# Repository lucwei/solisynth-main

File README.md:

# Solisynth
Solisynth is an open source modular synthesizer project. 

# License
The following license is used in the project, unless specified differently in a particular subfolder:

Schematics, PCBs: [CERN-OHL-S v2](https://ohwr.org/cern_ohl_s_v2.txt)

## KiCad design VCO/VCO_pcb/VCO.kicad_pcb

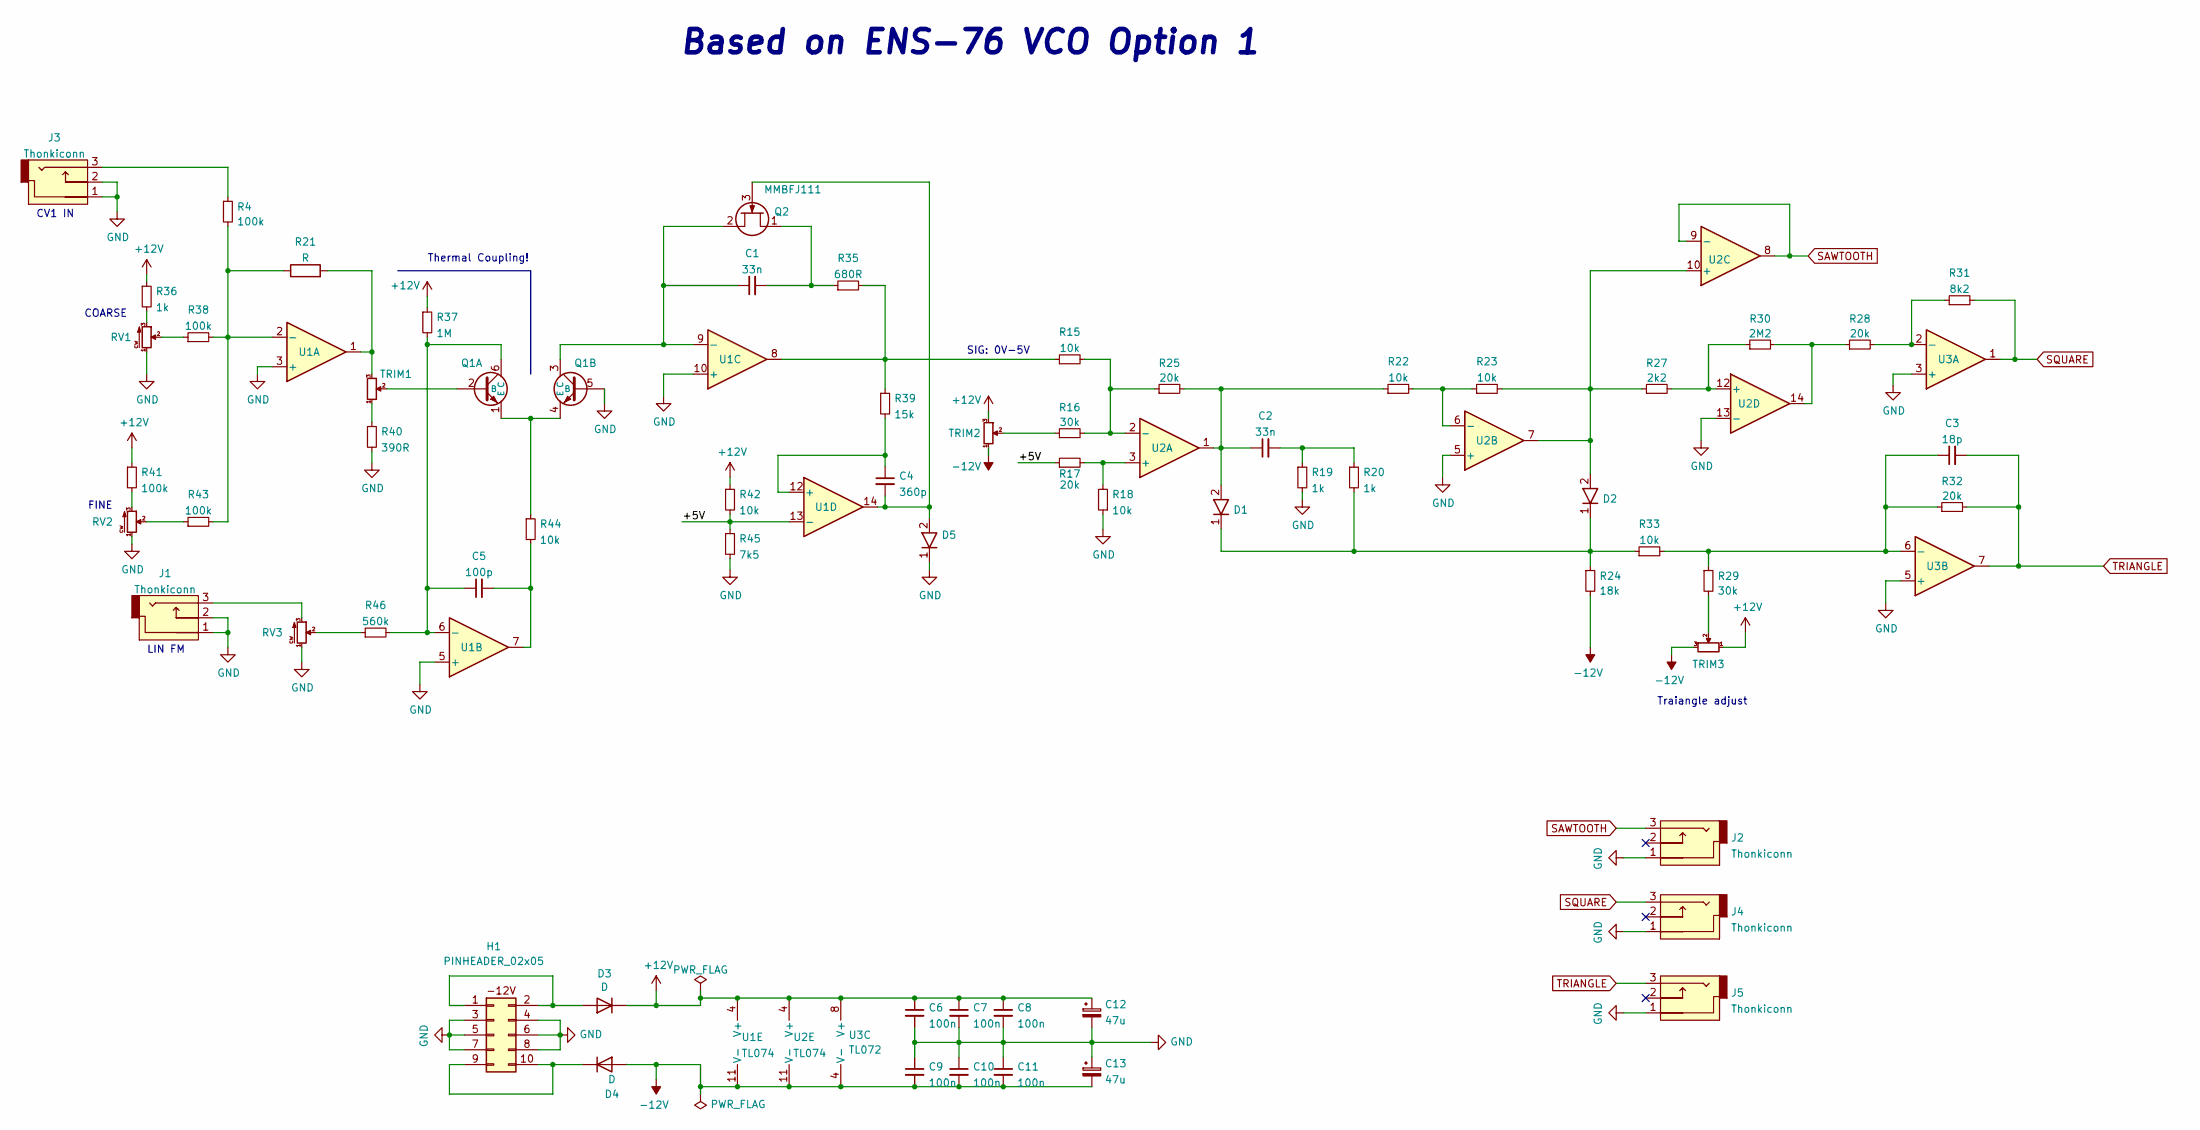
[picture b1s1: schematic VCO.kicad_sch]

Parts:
C1, C2: 33n; C_0603_1608Metric; Voltage 50V; Tolerance 10%; MPN CL10B333KB8NNNC
C3: 18p; C_0603_1608Metric; Voltage 50V; Tolerance 5%; MPN CL10C180JB81PNC
C4: 360p; C_0603_1608Metric; Voltage 50V; Tolerance 5%; MPN GRM1885C1H361JA01D
C5: 100p; C_0603_1608Metric; Voltage 50V; Tolerance 5%; MPN CL10C101JB8NNNC
C6, C7, C8, C9, C10, C11: 100n; C_0603_1608Metric; Voltage 50V; Tolerance 5%; MPN CL10B104JB8NNNC
C12, C13: 47u; CP_Elec_6.3x5.4; Voltage 25V; Tolerance 20%; MPN 865080443007
D1, D2, D5: D; SOD-123; MPN SBA130AS_R1_00001
D3, D4: D; D_SOD-123; MPN SBA130AS_R1_00001
H1: PINHEADER_02x05; Modular_Power_Header_2x05_P2.54mm_Vertical
J1, J2, J3, J4, J5: Thonkiconn; WQP-PJ398SM; MPN WQP-PJ398SM
Q1: BCM847BS,115; SOT65P210X110-6N; MPN BCM847BS,115
Q2: MMBFJ111; SOT-23; MPN MMBFJ111
R4, R38, R41, R43: 100k; R_0603_1608Metric; Tolerance 1%; MPN CR0603-FX-1003ELF
R15, R18, R22, R23, R33, R42, R44: 10k; R_0603_1608Metric; Tolerance 1%; MPN CR0603-FX-1002ELF
R16, R29: 30k; R_0603_1608Metric; Tolerance 1%; MPN CR0603-FX-3002ELF
R17: 20k; R_0603_1608Metric; MPN CR0603-FX-2002ELF; LCSC C4184
R19, R20, R36: 1k; R_0603_1608Metric; Tolerance 1%; MPN CR0603-FX-1001ELF
R21: R; R_Axial_DIN0204_L3.6mm_D1.6mm_P5.08mm_Horizontal; MPN TFPTL15L2201JL2B
R24: 18k; R_0603_1608Metric; Tolerance 1%; MPN CR0603-FX-1802ELF
R25, R28, R32: 20k; R_0603_1608Metric; Tolerance 1%; MPN CR0603-FX-2002ELF
R27: 2k2; R_0603_1608Metric; Tolerance 1%; MPN CR0603-FX-2201ELF
R30: 2M2; R_0603_1608Metric; Tolerance 1%; MPN RC0603FR-132M2L
R31: 8k2; R_0603_1608Metric; Tolerance 1%; MPN CR0603-FX-8201ELF; LCSC C114637
R35: 680R; R_0603_1608Metric; Tolerance 1%; MPN CR0603-FX-6800ELF
R37: 1M; R_0603_1608Metric; Tolerance 1%; MPN CR0603-FX-1004ELF
R39: 15k; R_0603_1608Metric; Tolerance 1%; MPN CR0603-FX-1502ELF
R40: 390R; R_0603_1608Metric; Tolerance 1%; MPN CR0603-FX-3900ELF
R45: 7k5; R_0603_1608Metric; Tolerance 1%; MPN CR0603-FX-7501ELF; LCSC C3016324
R46: 560k; R_0603_1608Metric; Tolerance 1%; MPN CR0603-FX-5603ELF
RV1: RK09L1140A66; RK09L; MPN RK09L1140A66
RV2, RV3: PTV09A-4025U-B103; PTV09A; MPN PTV09A-4025U-B103
TRIM1: 3362P-1-101LF; 3362P; MPN 3362P-1-101LF
TRIM2, TRIM3: 3362P-1-104LF; 3362P; MPN 3362P-1-104LF
U1, U2: TL074; SOIC-14_3.9x8.7mm_P1.27mm; MPN TL074
U3: TL072; SOIC-8_3.9x4.9mm_P1.27mm; MPN TL072

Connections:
+12V: C6.1, C7.1, C8.1, C12.1, D3.1 (K), R36.1, R37.1, R41.1, R42.1, TRIM2.3, TRIM3.1, U1.4 (V+), U2.4 (V+), U3.8 (V+)
-12V: C9.2, C10.2, C11.2, C13.2, D4.2 (A), R24.2, TRIM2.1, TRIM3.3, U1.11 (V-), U2.11 (V-), U3.4 (V-)
/+5V: R17.1, R42.2, R45.1, U1.13 (-)
GND: C6.2, C7.2, C8.2, C9.1, C10.1, C11.1, C12.2, C13.1, D5.1, H1.3, H1.4, H1.5, H1.6, H1.7, H1.8, J1.1, J1.2, J2.1, J3.1, J3.2, J4.1, J5.1, Q1.5 (B), R18.1, R19.2, R40.2, R45.2, RV1.1, RV2.1, RV3.1, U1.3 (+), U1.5 (+), U1.10 (+), U2.5 (+), U2.13 (-), U3.3 (+), U3.5 (+)
unnamed: C1.1, Q1.3 (C), Q2.2 (S), U1.9 (-)
unnamed: C1.2, Q2.1 (D), R35.1
unnamed: C2.1, D1.2, R22.1, R25.2, U2.1
unnamed: C2.2, R19.1, R20.1
unnamed: C3.1, R29.1, R32.1, R33.2, U3.6 (-)
unnamed: C4.1, R39.2, U1.12 (+)
unnamed: C4.2, D5.2, Q2.3 (G), U1.14
unnamed: C5.1, Q1.6 (C), R37.2, R46.2, U1.6 (-)
unnamed: C5.2, R44.2, U1.7
unnamed: D1.1, D2.1, R20.2, R24.1, R33.1
unnamed: D2.2, R23.2, R27.1, U2.7, U2.10 (+)
unnamed: D3.2 (A), H1.1, H1.2
unnamed: D4.1 (K), H1.9, H1.10
unnamed: J1.3, RV3.3
unnamed: J3.3, R4.1
unnamed: Q1.1 (E), Q1.4 (E), R44.1
unnamed: Q1.2 (B), TRIM1.2
unnamed: R15.1, R35.2, R39.1, U1.8
unnamed: R15.2, R16.2, R25.1, U2.2 (-)
unnamed: R16.1, TRIM2.2
unnamed: R17.2, R18.2, U2.3 (+)
unnamed: R4.2, R21.1, R38.2, R43.2, U1.2 (-)
unnamed: R21.2, TRIM1.3, U1.1
unnamed: R22.2, R23.1, U2.6 (-)
unnamed: R27.2, R30.1, U2.12 (+)
unnamed: R28.1, R30.2, U2.14
unnamed: R28.2, R31.1, U3.2 (-)
unnamed: R36.2, RV1.3
unnamed: R38.1, RV1.2
unnamed: R40.1, TRIM1.1
unnamed: R41.2, RV2.3
unnamed: R43.1, RV2.2
unnamed: R46.1, RV3.2
unnamed: R29.2, TRIM3.2
SAWTOOTH: J2.3, U2.8, U2.9 (-)
SQUARE: J4.3, R31.2, U3.1
TRIANGLE: C3.2, J5.3, R32.2, U3.7

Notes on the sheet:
CV1 IN
SIG: 0V-5V
Based on ENS-76 VCO Option 1
Traiangle adjust
FINE
LIN FM
COARSE
Thermal Coupling!

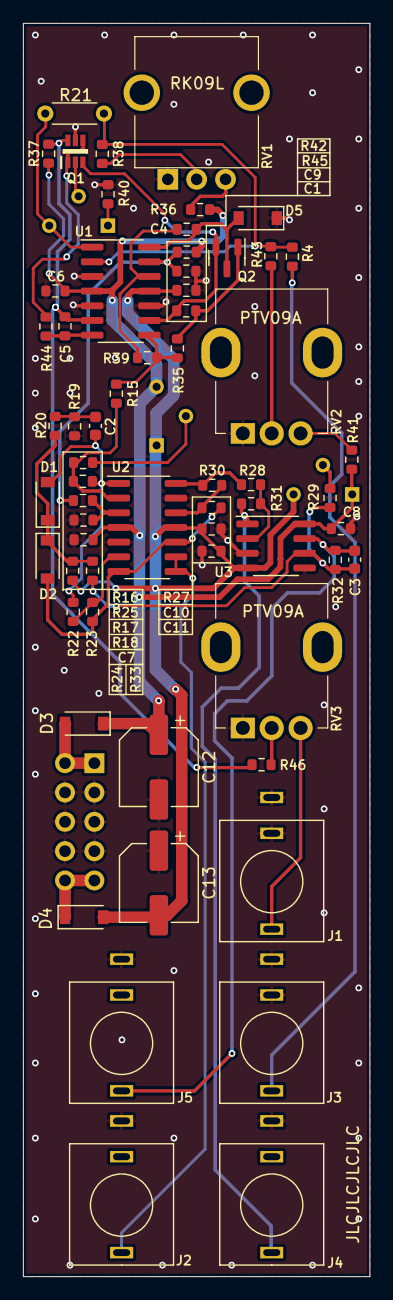
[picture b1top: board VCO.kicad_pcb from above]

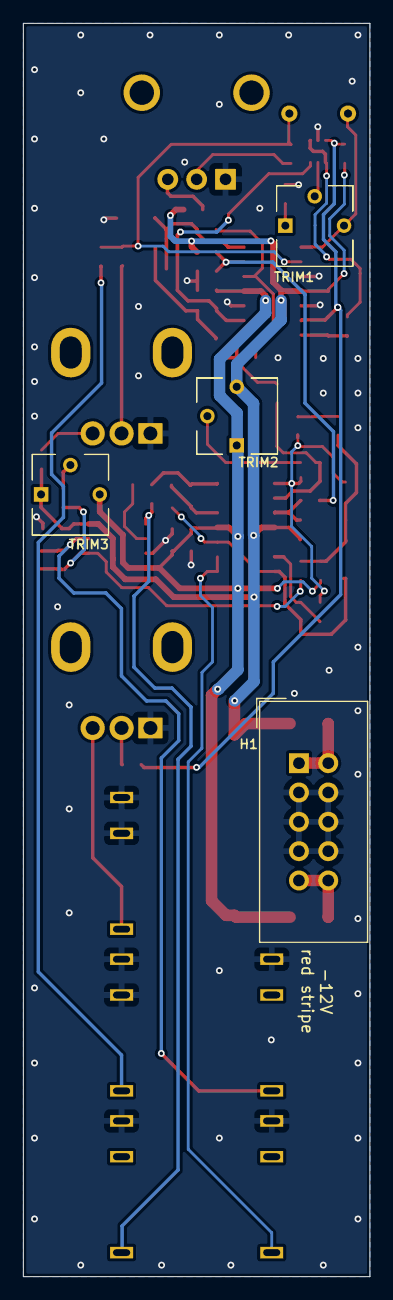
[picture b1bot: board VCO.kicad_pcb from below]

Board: 2 copper layers, 30.0 x 108.5 mm, 66 parts (4 on the bottom side), 41 nets.

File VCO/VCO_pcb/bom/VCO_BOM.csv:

VCO_V1 – BOM,,,,
Qty,Reference,Value,Manufacturer,Partnumber
2,"C1,C2",33n,Samsung Electro-Mechanics,CL10B333KB8NNNC
1,C3,18p,Samsung Electro-Mechanics,CL10C180JB81PNC
1,C4,360p,Murata Electronics,GRM1885C1H361JA01D
1,C5,100p,Samsung Electro-Mechanics,CL10C101JB8NNNC
6,C6-C11,100n,Samsung Electro-Mechanics,CL10B104JB8NNNC
2,"C12,C13",47u,Würth Elektronik,865080443007
5,"D1,D2,D3, D4,D5",SBA130AS_R1_00001,Panjit International Inc.,SBA130AS_R1_00001
1,H1,PINHEADER_02x05,Würth Elektronik,61201021621
5,J1-J5,Thonkiconn,Thonk,WQP-PJ398SM
1,Q1,"BCM847BS,115",Nexperia,"BCM847BS,115"
1,Q2,MMBFJ111,Onsemi,MMBFJ111
1,R16,30k,Bourns,CR0603-FX-3002ELF
3,"R19,R20,R36",1k,Bourns,CR0603-FX-1001ELF
1,R21,R,Vishay / Dale,TFPTL15L2201JL2B
7,"R15,R18,R22,R23,R33,R42,R44",10k,Bourns,CR0603-FX-1002ELF
1,R24,18k,Bourns,CR0603-FX-1802ELF
1,R27,2k2,Bourns,CR0603-FX-2201ELF
2,"R29,R37",1M,Bourns,CR0603-FX-1004ELF
1,R30,2M2,Yageo,RC0603FR-132M2L
1,R31,8k2,Bourns,CR0603-FX-8201ELF
4,"R17,R25,R28,R32",20k,Bourns,CR0603-FX-2002ELF
1,R35,680R,Bourns,CR0603-FX-6800ELF
1,R39,15k,Bourns,CR0603-FX-1502ELF
1,R40,390R,Bourns,CR0603-FX-3900ELF
4,"R4,R38,R41,R43",100k,Bourns,CR0603-FX-1003ELF
1,R45,7k5,Bourns,CR0603-FX-7501ELF
1,R46,560k,Bourns,CR0603-FX-5603ELF
1,RV1,RK09L1140A66,Alps,RK09L1140A66
2,"RV2,RV3",PTV09A-4025U-B103,Bourns,PTV09A-4025U-B103
1,TRIM1,3362P-1-101LF,Bourns,3362P-1-101LF
2,"TRIM2,TRIM3",3362P-1-104LF,Bourns,3362P-1-104LF
2,"U1,U2",TL074,Texas Instruments,TL074
1,U3,TL072,Texas Instruments,TL072
,,,,
,,,,
,,,,
Cable,,,,
1,,PINHEADER_FEMALE_02x08,Würth Elektronik,61201623021
1,,PINHEADER_FEMALE_02x05,Würth Elektronik,61201023021
1,,Flatband cable 10cm,,

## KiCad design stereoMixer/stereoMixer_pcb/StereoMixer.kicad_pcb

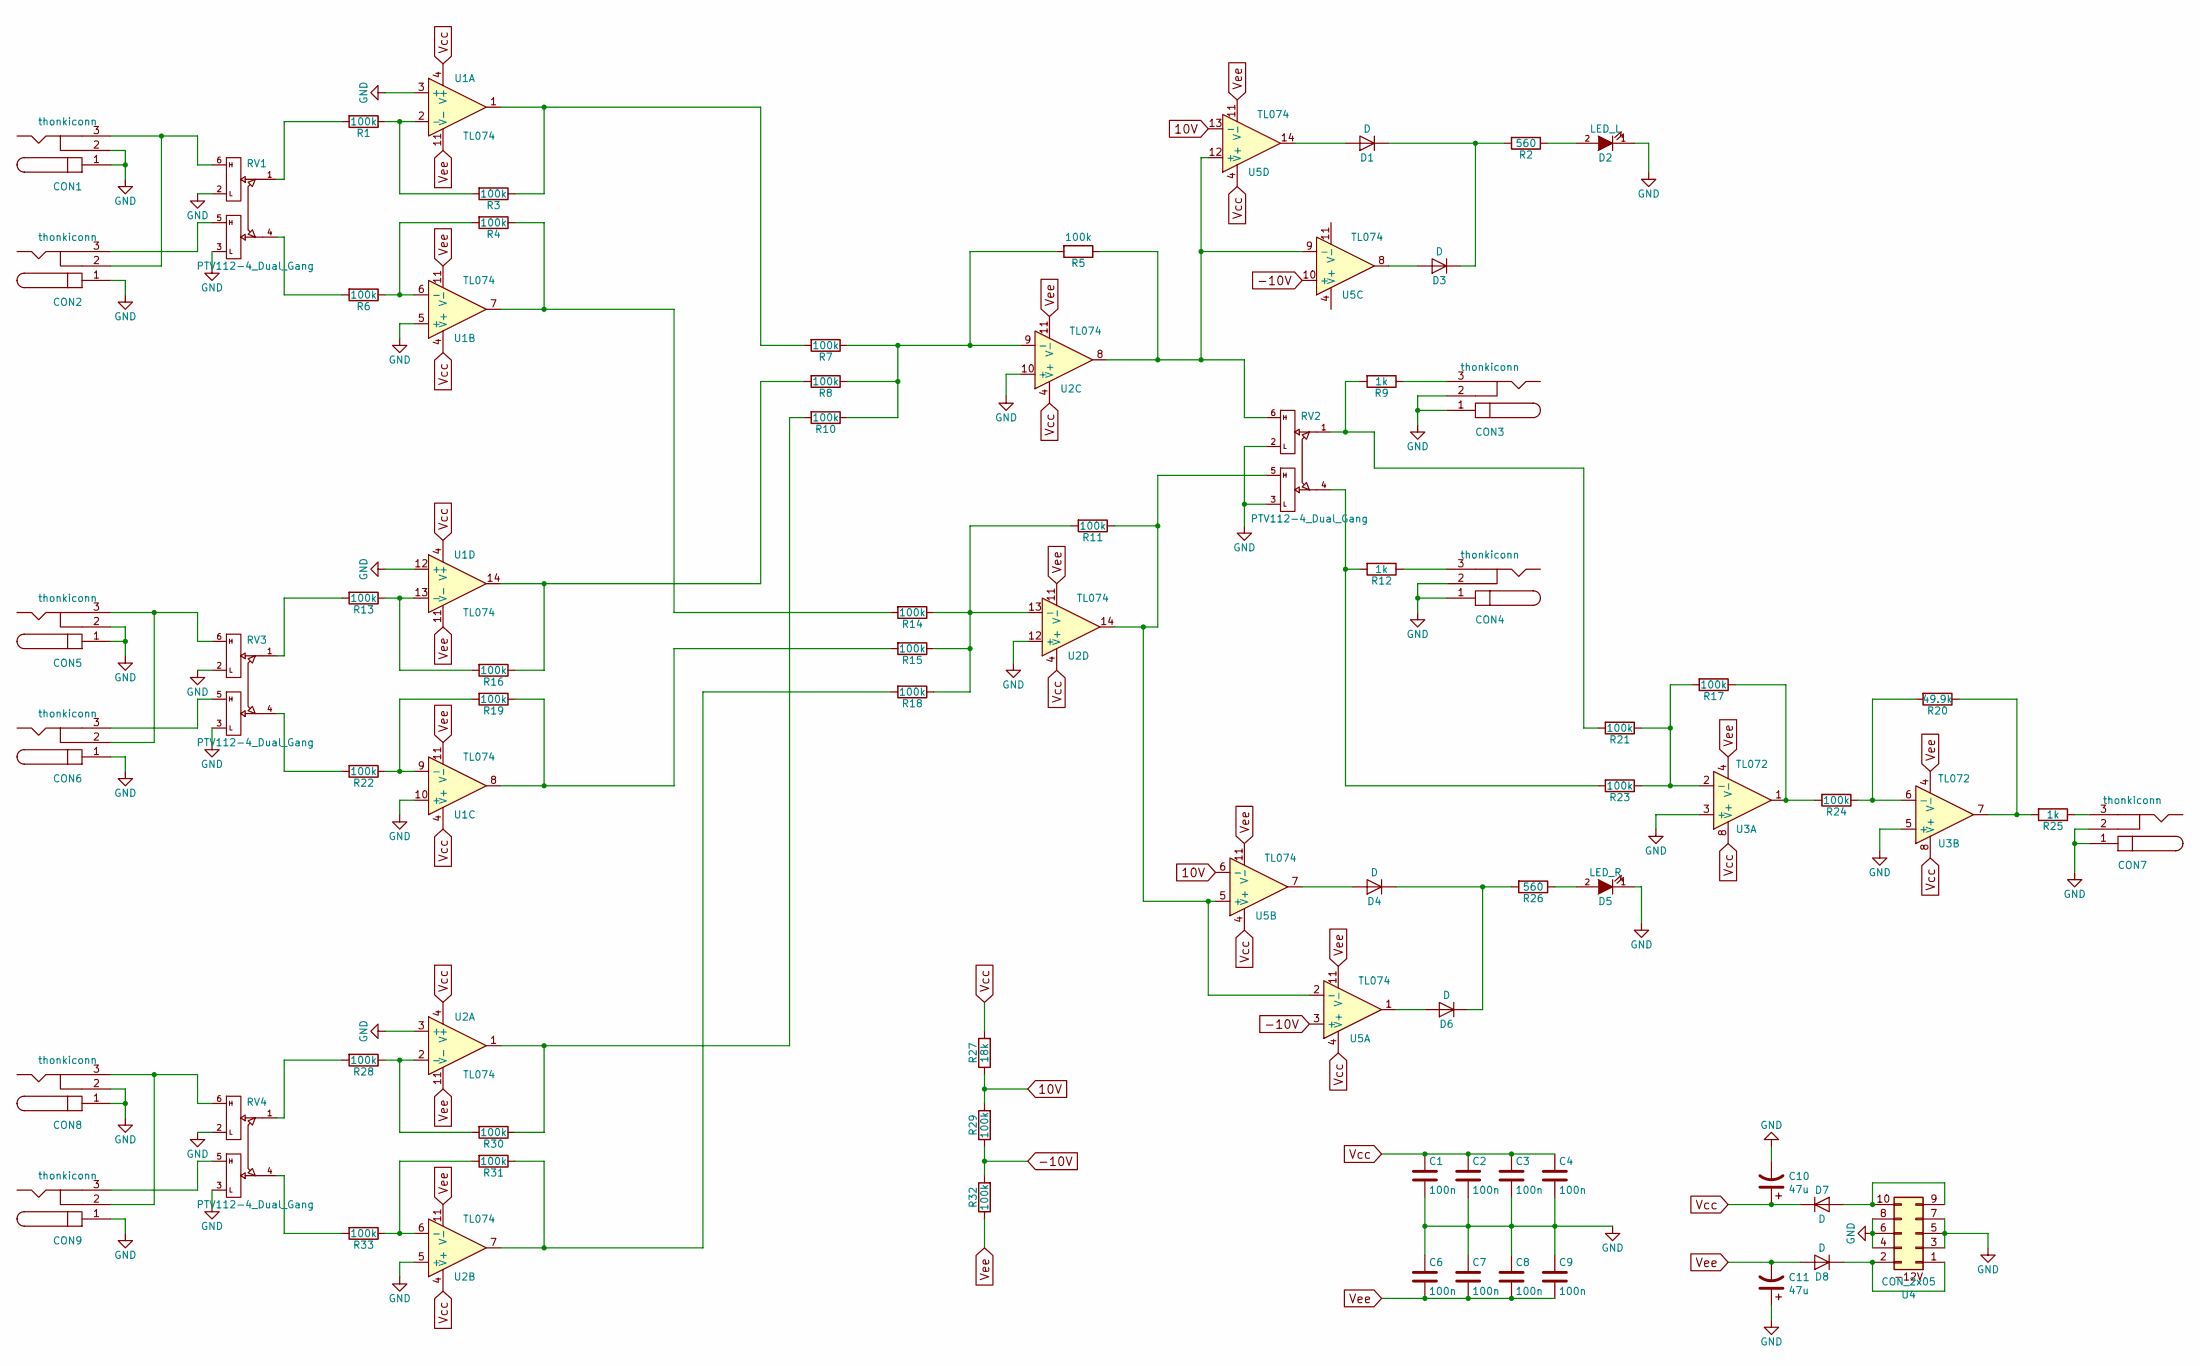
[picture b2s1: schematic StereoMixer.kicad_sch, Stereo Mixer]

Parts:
C1, C2, C3, C4, C6, C7, C8, C9: 100n; C_0603_HandSoldering
C10, C11: 47u; CP_Elec_5x3.9
CON1, CON2, CON3, CON4, CON5, CON6, CON7, CON8, CON9: thonkiconn; THONKICONN
D1, D3, D4, D6, D7, D8: D; D_0603_1608Metric_Pad1.05x0.95mm_HandSolder
D2: LED_L; LED_D3.0mm
D5: LED_R; LED_D3.0mm
R1, R3, R4, R5, R6, R7, R8, R10, R11, R13, R14, R15, R16, R17, R18, R19, R21, R22, R23, R24, R28, R29, R30, R31, R32, R33: 100k; R_0603_HandSoldering
R2, R26: 560; R_0603_HandSoldering
R9, R12, R25: 1k; R_0603_HandSoldering
R20: 49.9k; R_0603_HandSoldering
R27: 18k; R_0603_HandSoldering
RV1, RV2, RV3, RV4: PTV112-4_Dual_Gang; PTV112
U1, U2, U5: TL074; SOIC-14_3.9x8.7mm_Pitch1.27mm
U3: TL072; SOIC-8_3.9x4.9mm_P1.27mm
U4: CON_2x05; Modular_Power_Header_2x05_P2.54mm_Vertical

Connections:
10V: R27.1, R29.2, U5.6 (-), U5.13 (-)
-10V: R29.1, R32.2, U5.3 (+), U5.10 (+)
unnamed: CON1.3, CON2.2, RV1.6
unnamed: CON2.3, RV1.5
unnamed: CON3.3, R9.1
unnamed: CON4.3, R12.1
unnamed: CON5.3, CON6.2, RV3.6
unnamed: CON6.3, RV3.5
unnamed: CON7.3, R25.1
unnamed: CON8.3, CON9.2, RV4.6
unnamed: CON9.3, RV4.5
unnamed: D1.1 (K), D3.1 (K), R2.2
unnamed: D1.2 (A), U5.14
unnamed: D2.2 (A), R2.1
unnamed: D3.2 (A), U5.8
unnamed: D4.1 (K), D6.1 (K), R26.2
unnamed: D4.2 (A), U5.7
unnamed: D5.2 (A), R26.1
unnamed: D6.2 (A), U5.1
unnamed: D7.2 (A), U4.9, U4.10
unnamed: D8.1 (K), U4.1, U4.2
unnamed: R1.1, R3.2, U1.2 (-)
unnamed: R1.2, RV1.1
unnamed: R3.1, R7.2, U1.1
unnamed: R4.2, R6.1, U1.6 (-)
unnamed: R5.1, RV2.6, U2.8, U5.9 (-), U5.12 (+)
unnamed: R6.2, RV1.4
unnamed: R5.2, R7.1, R8.1, R10.1, U2.9 (-)
unnamed: R10.2, R30.1, U2.1
unnamed: R11.1, RV2.5, U2.14, U5.2 (-), U5.5 (+)
unnamed: R11.2, R14.1, R15.1, R18.1, U2.13 (-)
unnamed: R12.2, R23.2, RV2.4
unnamed: R13.1, R16.2, U1.13 (-)
unnamed: R13.2, RV3.1
unnamed: R4.1, R14.2, U1.7
unnamed: R15.2, R19.1, U1.8
unnamed: R8.2, R16.1, U1.14
unnamed: R17.1, R24.2, U3.1
unnamed: R17.2, R21.1, R23.1, U3.2 (-)
unnamed: R18.2, R31.1, U2.7
unnamed: R19.2, R22.1, U1.9 (-)
unnamed: R20.1, R25.2, U3.7
unnamed: R20.2, R24.1, U3.6 (-)
unnamed: R9.2, R21.2, RV2.1
unnamed: R22.2, RV3.4
unnamed: R28.1, R30.2, U2.2 (-)
unnamed: R28.2, RV4.1
unnamed: R31.2, R33.1, U2.6 (-)
unnamed: R33.2, RV4.4
Vcc: C1.1, C2.1, C3.1, C4.1, C10.1, D7.1 (K), R27.2, U1.4 (V+), U2.4 (V+), U3.8 (V+), U5.4 (V+)
Vee: C6.2, C7.2, C8.2, C9.2, C11.2, D8.2 (A), R32.1, U1.11 (V-), U2.11 (V-), U3.4 (V-), U5.11 (V-)

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
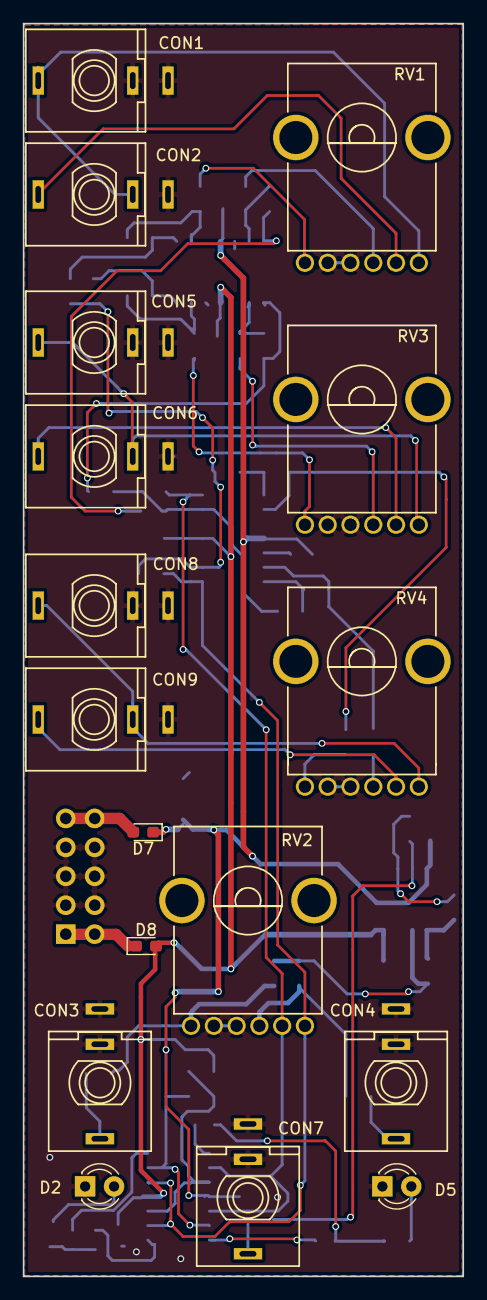
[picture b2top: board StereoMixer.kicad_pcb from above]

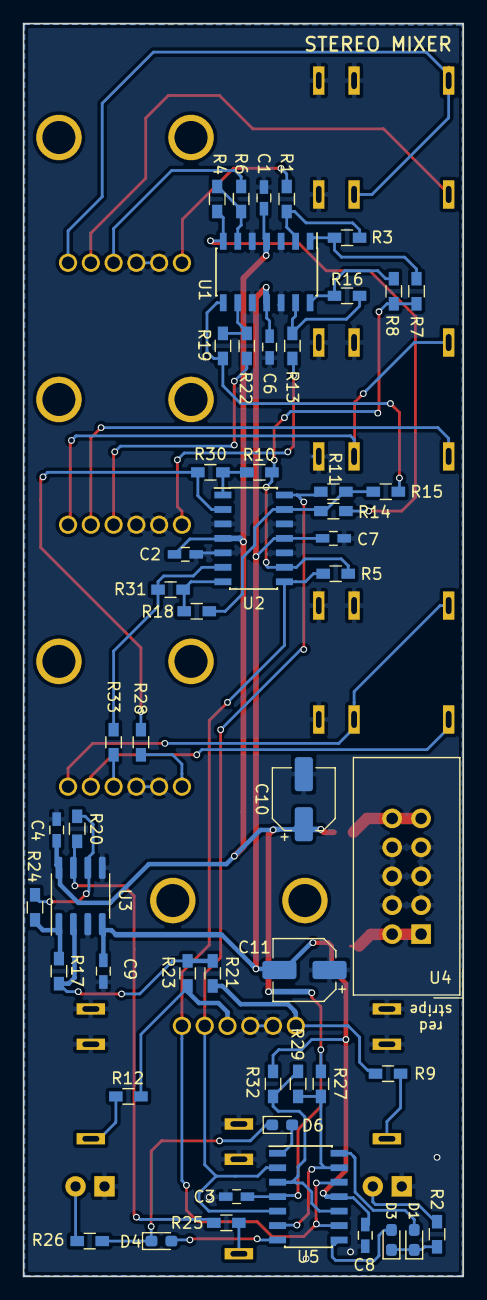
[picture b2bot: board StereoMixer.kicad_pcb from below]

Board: 2 copper layers, 38.6 x 110.0 mm, 69 parts (52 on the bottom side), 52 nets.

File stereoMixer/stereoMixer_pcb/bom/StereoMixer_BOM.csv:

Qty,Reference,Value,Manufcaturer Name,Manufacturer Partnumber
8,"C1-C4,C6-C9",100n,Kemet,C0603C104M5RACTU
2,"C10,C11",47u,Würth Elektronik,865080342006
9,CON1-CON9,thonkiconn,,thonkiconn
2,"D2,D5",LED_L/LED_R,Lite-On,LTL-4291
6,"D1,D3,D4,D6,D7,D8",D,Comchip,CDBU0320
1,P1,CONN_02X05,Würth Elektronik,61201021621
2,"R2,R26",560R,Vishay / Dale,CRCW0603560RFKEA
26,"R1,R3-R8,R10,R11,R13-R19,R21-R24,R28-R33",100k,Vishay / Dale,CRCW0603100KFKEAC
3,"R9,R12,R25",1k,Vishay / Dale,CRCW06031K00FKEAC
1,R20,49.9k,Vishay / Dale,CRCW060349K9FKEAC
1,R27,18k,Vishay / Dale,CRCW0603-18K-E3
4,RV1-RV4,PTV112-4_Dual_Gang,Bourns,PTV112-4420A-A503
3,"U1,U2,U5",TL074,Texas Instruments,TL074IDR
1,U3,TL072,Texas Instruments,TlL072CDR

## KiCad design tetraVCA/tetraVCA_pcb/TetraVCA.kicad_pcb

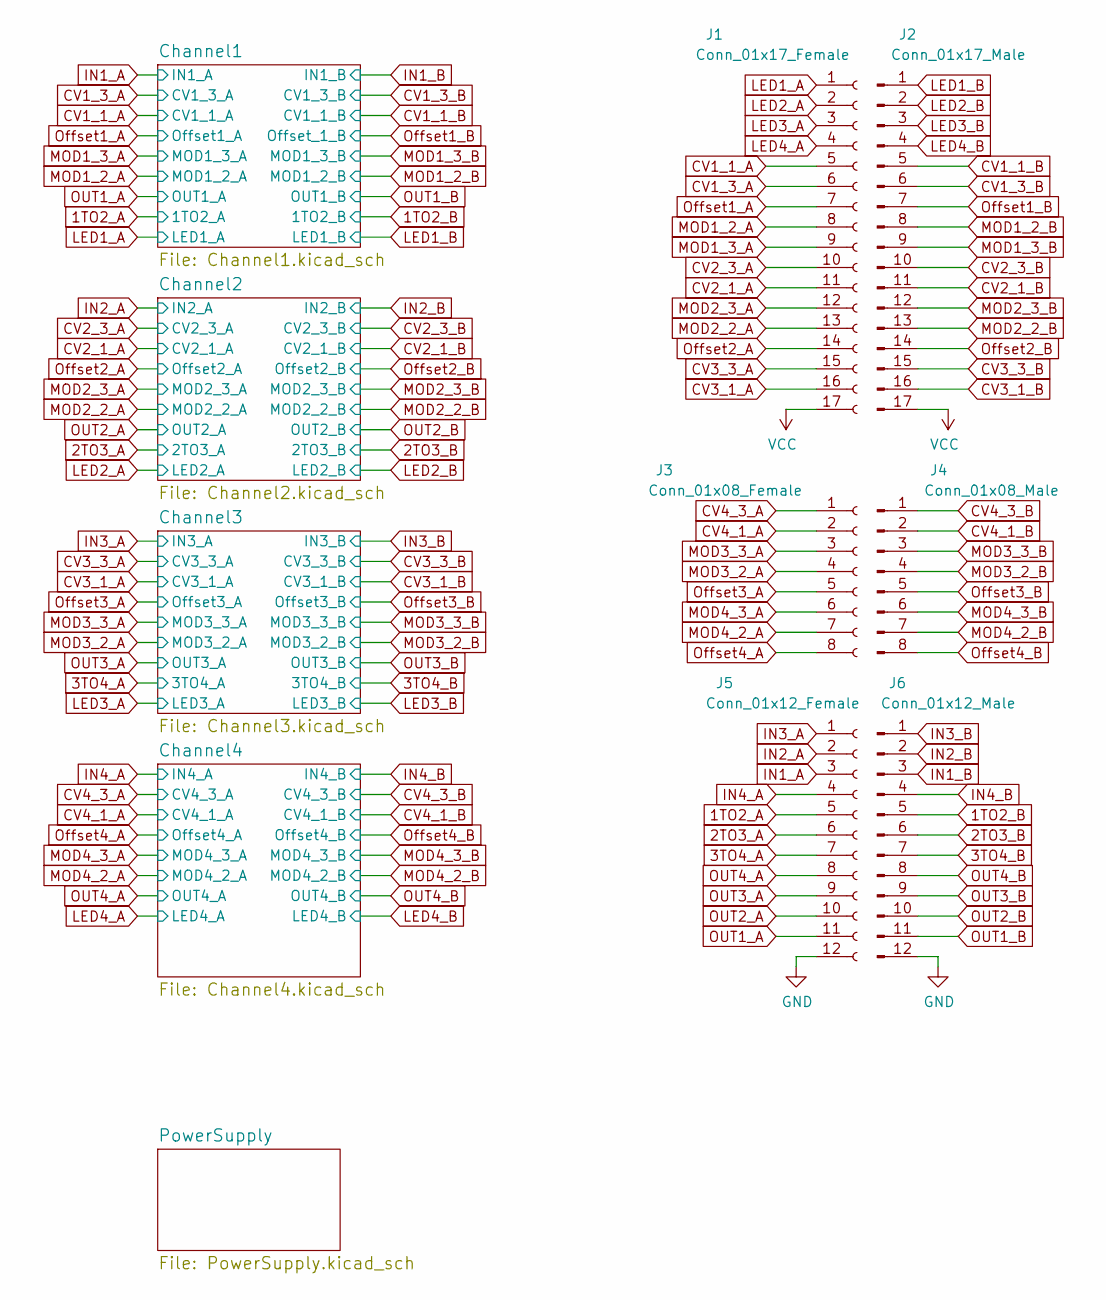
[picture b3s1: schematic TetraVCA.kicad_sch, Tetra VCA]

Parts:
J1: Conn_01x17_Female; PinSocket_1x17_P2.54mm_Vertical
J2: Conn_01x17_Male; PinHeader_1x17_P2.54mm_Vertical
J3: Conn_01x08_Female; PinSocket_1x08_P2.54mm_Vertical
J4: Conn_01x08_Male; PinHeader_1x08_P2.54mm_Vertical
J5: Conn_01x12_Female; PinSocket_1x12_P2.54mm_Vertical
J6: Conn_01x12_Male; PinHeader_1x12_P2.54mm_Vertical

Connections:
1TO2_A: J5.5; also elsewhere on the board
1TO2_B: J6.5; also elsewhere on the board
2TO3_A: J5.6; also elsewhere on the board
2TO3_B: J6.6; also elsewhere on the board
3TO4_A: J5.7; also elsewhere on the board
3TO4_B: J6.7; also elsewhere on the board
CV1_1_A: J1.5; also elsewhere on the board
CV1_1_B: J2.5; also elsewhere on the board
CV1_3_A: J1.6; also elsewhere on the board
CV1_3_B: J2.6; also elsewhere on the board
CV2_1_A: J1.11; also elsewhere on the board
CV2_1_B: J2.11; also elsewhere on the board
CV2_3_A: J1.10; also elsewhere on the board
CV2_3_B: J2.10; also elsewhere on the board
CV3_1_A: J1.16; also elsewhere on the board
CV3_1_B: J2.16; also elsewhere on the board
CV3_3_A: J1.15; also elsewhere on the board
CV3_3_B: J2.15; also elsewhere on the board
CV4_1_A: J3.2; also elsewhere on the board
CV4_1_B: J4.2; also elsewhere on the board
CV4_3_A: J3.1; also elsewhere on the board
CV4_3_B: J4.1; also elsewhere on the board
GND: J5.12, J6.12; also elsewhere on the board
IN1_A: J5.3; also elsewhere on the board
IN1_B: J6.3; also elsewhere on the board
IN2_A: J5.2; also elsewhere on the board
IN2_B: J6.2; also elsewhere on the board
IN3_A: J5.1; also elsewhere on the board
IN3_B: J6.1; also elsewhere on the board
IN4_A: J5.4; also elsewhere on the board
IN4_B: J6.4; also elsewhere on the board
LED1_A: J1.1; also elsewhere on the board
LED1_B: J2.1; also elsewhere on the board
LED2_A: J1.2; also elsewhere on the board
LED2_B: J2.2; also elsewhere on the board
LED3_A: J1.3; also elsewhere on the board
LED3_B: J2.3; also elsewhere on the board
LED4_A: J1.4; also elsewhere on the board
LED4_B: J2.4; also elsewhere on the board
MOD1_2_A: J1.8; also elsewhere on the board
MOD1_2_B: J2.8; also elsewhere on the board
MOD1_3_A: J1.9; also elsewhere on the board
MOD1_3_B: J2.9; also elsewhere on the board
MOD2_2_A: J1.13; also elsewhere on the board
MOD2_2_B: J2.13; also elsewhere on the board
MOD2_3_A: J1.12; also elsewhere on the board
MOD2_3_B: J2.12; also elsewhere on the board
MOD3_2_A: J3.4; also elsewhere on the board
MOD3_2_B: J4.4; also elsewhere on the board
MOD3_3_A: J3.3; also elsewhere on the board
MOD3_3_B: J4.3; also elsewhere on the board
MOD4_2_A: J3.7; also elsewhere on the board
MOD4_2_B: J4.7; also elsewhere on the board
MOD4_3_A: J3.6; also elsewhere on the board
MOD4_3_B: J4.6; also elsewhere on the board
OUT1_A: J5.11; also elsewhere on the board
OUT1_B: J6.11; also elsewhere on the board
OUT2_A: J5.10; also elsewhere on the board
OUT2_B: J6.10; also elsewhere on the board
OUT3_A: J5.9; also elsewhere on the board
OUT3_B: J6.9; also elsewhere on the board
OUT4_A: J5.8; also elsewhere on the board
OUT4_B: J6.8; also elsewhere on the board
Offset1_A: J1.7; also elsewhere on the board
Offset1_B: J2.7; also elsewhere on the board
Offset2_A: J1.14; also elsewhere on the board
Offset2_B: J2.14; also elsewhere on the board
Offset3_A: J3.5; also elsewhere on the board
Offset3_B: J4.5; also elsewhere on the board
Offset4_A: J3.8; also elsewhere on the board
Offset4_B: J4.8; also elsewhere on the board
VCC: J1.17, J2.17; also elsewhere on the board

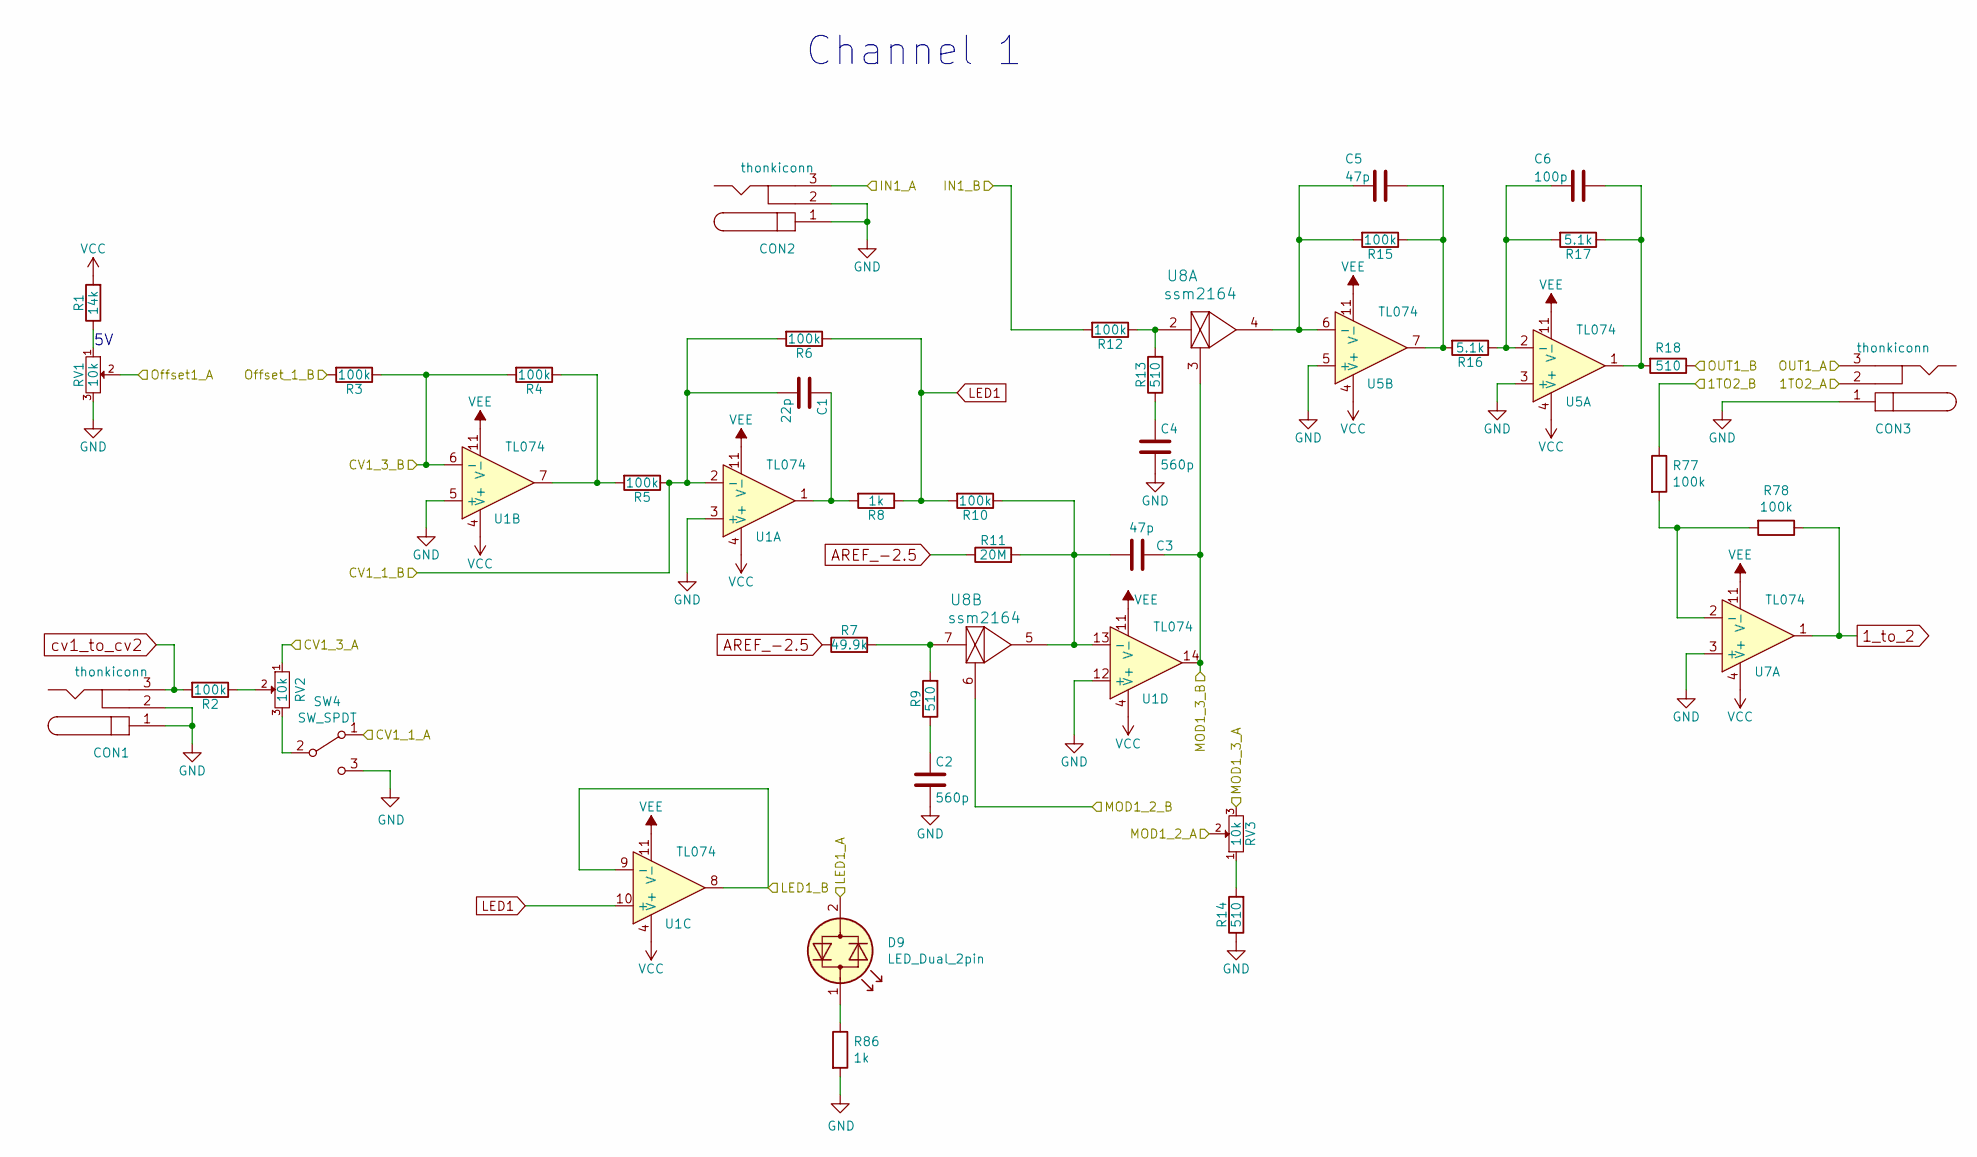
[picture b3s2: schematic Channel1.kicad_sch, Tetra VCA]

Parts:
C1: 22p; C_0603_1608Metric_Pad1.05x0.95mm_HandSolder
C2, C4: 560p; C_0603_1608Metric_Pad1.05x0.95mm_HandSolder
C3, C5: 47p; C_0603_1608Metric_Pad1.05x0.95mm_HandSolder
C6: 100p; C_0603_1608Metric_Pad1.05x0.95mm_HandSolder
CON1, CON2, CON3: thonkiconn; MPN PJ398SM
D9: LED_Dual_2pin; LED_D3.0mm; MPN LTL-10CHJ
R1: 14k; R_0603_1608Metric_Pad1.05x0.95mm_HandSolder
R2, R3, R4, R5, R6, R10, R12, R15, R77, R78: 100k; R_0603_1608Metric_Pad1.05x0.95mm_HandSolder
R7: 49.9k; R_0603_1608Metric_Pad1.05x0.95mm_HandSolder
R8, R86: 1k; R_0603_1608Metric_Pad1.05x0.95mm_HandSolder
R9, R13, R14, R18: 510; R_0603_1608Metric_Pad1.05x0.95mm_HandSolder
R11: 20M; R_0603_1608Metric_Pad1.05x0.95mm_HandSolder
R16, R17: 5.1k; R_0603_1608Metric_Pad1.05x0.95mm_HandSolder
RV1: 10k; Potentiometer_Alps_RK09K_Single_Vertical; MPN RK09L1140A5E
RV2, RV3: 10k; Potentiometer_Alps_RK09K_Single_Vertical; MPN PTV09A-4025U-B103
SW4: SW_SPDT; Switch_EG1249; MPN EG1248
U1, U5, U7: TL074; SOIC-14_3.9x8.7mm_P1.27mm; MPN TL074
U8: ssm2164; SOIC-16_3.9x9.9mm_P1.27mm; MPN SSM2164

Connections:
1TO2_A: CON3.2; also elsewhere on the board
1TO2_B: R77.1; also elsewhere on the board
1_to_2: R78.1, U7.1; also elsewhere on the board
AREF_-2.5: R7.1, R11.1; also elsewhere on the board
CV1_1_A: SW4.1 (A); also elsewhere on the board
CV1_1_B: C1.2, R5.1, R6.2, U1.2 (-); also elsewhere on the board
CV1_3_A: RV2.1; also elsewhere on the board
CV1_3_B: R3.1, R4.2, U1.6 (-); also elsewhere on the board
GND: C2.2, C4.2, CON1.1, CON1.2, CON2.1, CON2.2, CON3.1, R14.1, R86.2, RV1.3, SW4.3 (C), U1.3 (+), U1.5 (+), U1.12 (+), U5.3 (+), U5.5 (+), U7.3 (+); also elsewhere on the board
IN1_A: CON2.3; also elsewhere on the board
IN1_B: R12.2; also elsewhere on the board
LED1: R6.1, R8.1, R10.2, U1.10 (+)
LED1_A: D9.2 (AK); also elsewhere on the board
LED1_B: U1.8, U1.9 (-); also elsewhere on the board
MOD1_2_A: RV3.2; also elsewhere on the board
MOD1_2_B: U8.6; also elsewhere on the board
MOD1_3_A: RV3.3; also elsewhere on the board
MOD1_3_B: C3.1, U1.14, U8.3; also elsewhere on the board
unnamed: C1.1, R8.2, U1.1
unnamed: C2.1, R9.1
unnamed: C3.2, R10.1, R11.2, U1.13 (-), U8.5
unnamed: C4.1, R13.1
unnamed: C5.1, R15.1, R16.2, U5.7
unnamed: C5.2, R15.2, U5.6 (-), U8.4
unnamed: C6.1, R17.1, R18.2, U5.1
unnamed: C6.2, R16.1, R17.2, U5.2 (-)
unnamed: D9.1 (KA), R86.1
unnamed: R1.1, RV1.1
unnamed: R2.1, RV2.2
unnamed: R4.1, R5.2, U1.7
unnamed: R7.2, R9.2, U8.7
unnamed: R12.1, R13.2, U8.2
unnamed: R14.2, RV3.1
unnamed: R77.2, R78.2, U7.2 (-)
unnamed: RV2.3, SW4.2 (B)
OUT1_A: CON3.3; also elsewhere on the board
OUT1_B: R18.1; also elsewhere on the board
Offset1_A: RV1.2; also elsewhere on the board
Offset1_B: R3.2; also elsewhere on the board
VCC: R1.2, U1.4 (V+), U5.4 (V+), U7.4 (V+); also elsewhere on the board
VEE: U1.11 (V-), U5.11 (V-), U7.11 (V-); also elsewhere on the board
cv1_to_cv2: CON1.3, R2.2; also elsewhere on the board

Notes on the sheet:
Channel 1
